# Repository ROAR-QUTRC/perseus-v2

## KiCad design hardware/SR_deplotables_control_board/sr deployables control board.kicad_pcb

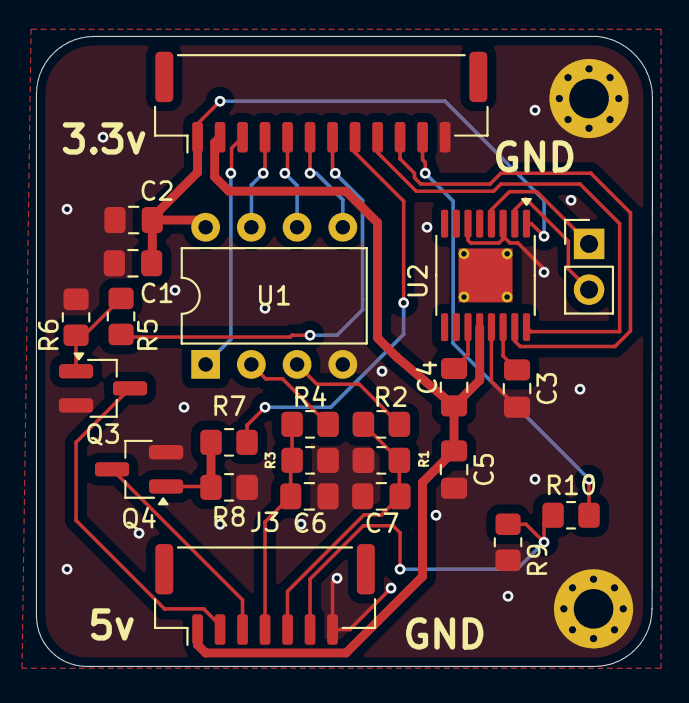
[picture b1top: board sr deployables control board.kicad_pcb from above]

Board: 2 copper layers, 34.2 x 35.0 mm, 26 parts (0 on the bottom side), 25 nets.

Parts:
C1: 100nF; C_0805_2012Metric_Pad1.18x1.45mm_HandSolder
C2, C6, C7: 10nF; C_0805_2012Metric_Pad1.18x1.45mm_HandSolder
C3: 2.2uF 6.3v; C_0805_2012Metric_Pad1.18x1.45mm_HandSolder
C4: 0.01uF, 16v ceramic X7R; C_0805_2012Metric_Pad1.18x1.45mm_HandSolder
C5: 10uF; C_0805_2012Metric_Pad1.18x1.45mm_HandSolder
H1: M1; MountingHole_2.2mm_M2_Pad_Via
H2: M2; MountingHole_2.2mm_M2_Pad_Via
J1: Conn_01x12_Pin; JST_GH_BM12B-GHS-TBT_1x12-1MP_P1.25mm_Vertical
J2: Conn_01x02_Pin; PinHeader_1x02_P2.54mm_Vertical
J3: Conn_01x07_Pin; JST_GH_BM07B-GHS-TBT_1x07-1MP_P1.25mm_Vertical
Q3, Q4: 2N7002; SOT-23_Handsoldering
R1, R3, R6, R8, R9: 10k; R_0805_2012Metric_Pad1.20x1.40mm_HandSolder
R2, R4, R10: 20k; R_0805_2012Metric_Pad1.20x1.40mm_HandSolder
R5, R7: 100; R_0805_2012Metric_Pad1.20x1.40mm_HandSolder
U1: MCP3002; DIP-8_W7.62mm
U2: DRV8833PW; TSSOP-16-1EP_4.4x5mm_P0.65mm_EP3x3mm_ThermalVias

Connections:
+3.3V: C1.1, C2.1, J1.1, U1.8 (VDD/VREF), U2.1 (~SLEEP)
AIN1: J1.9, U2.16 (AIN1)
AIN2: J1.10, U2.15 (AIN2)
CH0: C6.1, J3.4, R3.1, R4.1
CH1: C7.2, J3.5, R1.2, R2.1
CLK: J1.4, U1.7 (CLK)
CS: J1.3, U1.1 (~CS/SHDN)
DRAIN1: J3.2, Q3.3 (D)
DRAIN2: J3.3, Q4.3 (D)
GATE1: J1.7, R5.1
GATE2: J1.8, R7.1
GND: C1.2, C2.2, C3.2, C5.2, C6.2, C7.1, H1.1, H2.1, J1.12, J3.7, Q3.2 (S), Q4.2 (S), R1.1, R3.2, R6.1, R8.1, R9.2, U1.4 (VSS), U2.3 (AISEN), U2.6 (BISEN), U2.13 (GND)
MISO: J1.5, U1.6 (DOUT)
MOSI: J1.6, U1.5 (DIN)
unnamed: J2.1, U2.4 (AOUT2)
unnamed: J2.2, U2.2 (AOUT1)
unnamed: J3.6, R9.1, R10.1
unnamed: Q3.1 (G), R5.2, R6.2
unnamed: Q4.1 (G), R7.2, R8.2
unnamed: R4.2, U1.2 (CH0)
unnamed: R2.2, U1.3 (CH1)
unnamed: C4.2, U2.11 (VCP)
unnamed: C3.1, U2.14 (VINT)
SWITCH: J1.11, R10.2
VM: C4.1, C5.1, J1.2, J3.1, U2.12 (VM)

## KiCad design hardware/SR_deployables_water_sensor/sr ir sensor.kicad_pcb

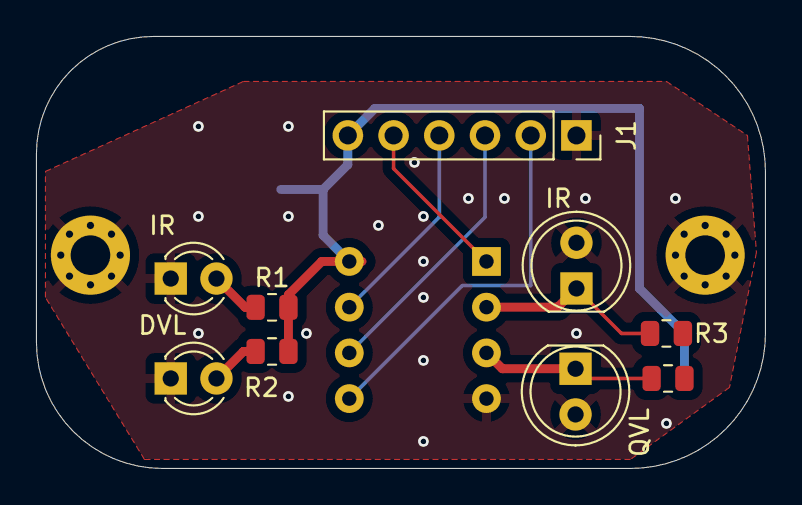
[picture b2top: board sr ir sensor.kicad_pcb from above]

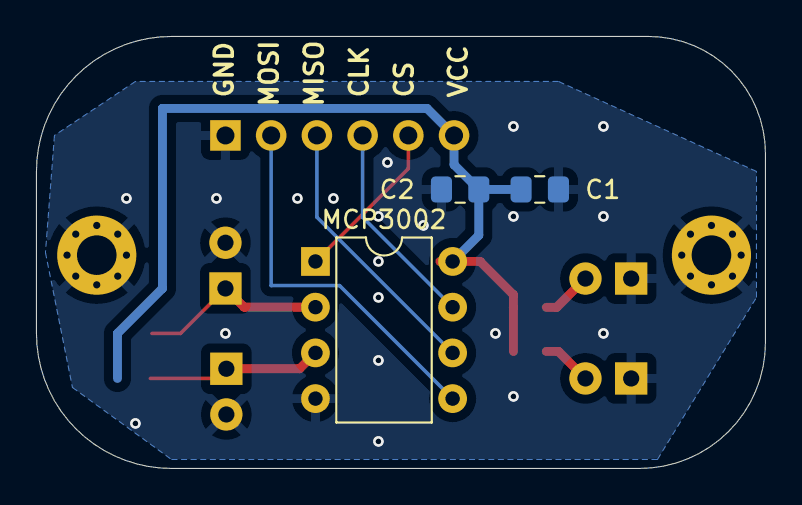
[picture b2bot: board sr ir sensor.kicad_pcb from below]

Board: 2 copper layers, 40.5 x 24.0 mm, 14 parts (3 on the bottom side), 10 nets.

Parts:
C1: 100nF; C_0805_2012Metric_Pad1.18x1.45mm_HandSolder
C2: 10nF; C_0805_2012Metric_Pad1.18x1.45mm_HandSolder
DVL: LED; LED_D3.0mm_Clear
H1: M1; MountingHole_2.2mm_M2_Pad_Via
H2: M2; MountingHole_2.2mm_M2_Pad_Via
IR: BPW40; LED_D5.0mm_Clear
IR#2: LED; LED_D3.0mm_Clear
J1: Pin_Connector; PinSocket_1x06_P2.54mm_Vertical
MCP3002: MCP3002; DIP-8_W7.62mm
QVL: BPW40; LED_D5.0mm_Clear
R1, R2, R3, R4: R; R_0805_2012Metric

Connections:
+3.3V: C1.1, C2.1, J1.6, MCP3002.8 (VDD/VREF), R1.2, R2.2, R3.2, R4.2
CH0: IR.1 (C), MCP3002.2 (CH0), R4.1
CH1: MCP3002.3 (CH1), QVL.1 (C), R3.1
CLK: J1.4, MCP3002.7 (CLK)
CS: J1.5, MCP3002.1 (~CS/SHDN)
GND: C1.2, C2.2, DVL.1 (K), H1.1, H2.1, IR.2 (E), IR#2.1 (K), J1.1, MCP3002.4 (VSS), QVL.2 (E)
MISO: J1.3, MCP3002.6 (DOUT)
MOSI: J1.2, MCP3002.5 (DIN)
unnamed: IR#2.2 (A), R1.1
unnamed: DVL.2 (A), R2.1

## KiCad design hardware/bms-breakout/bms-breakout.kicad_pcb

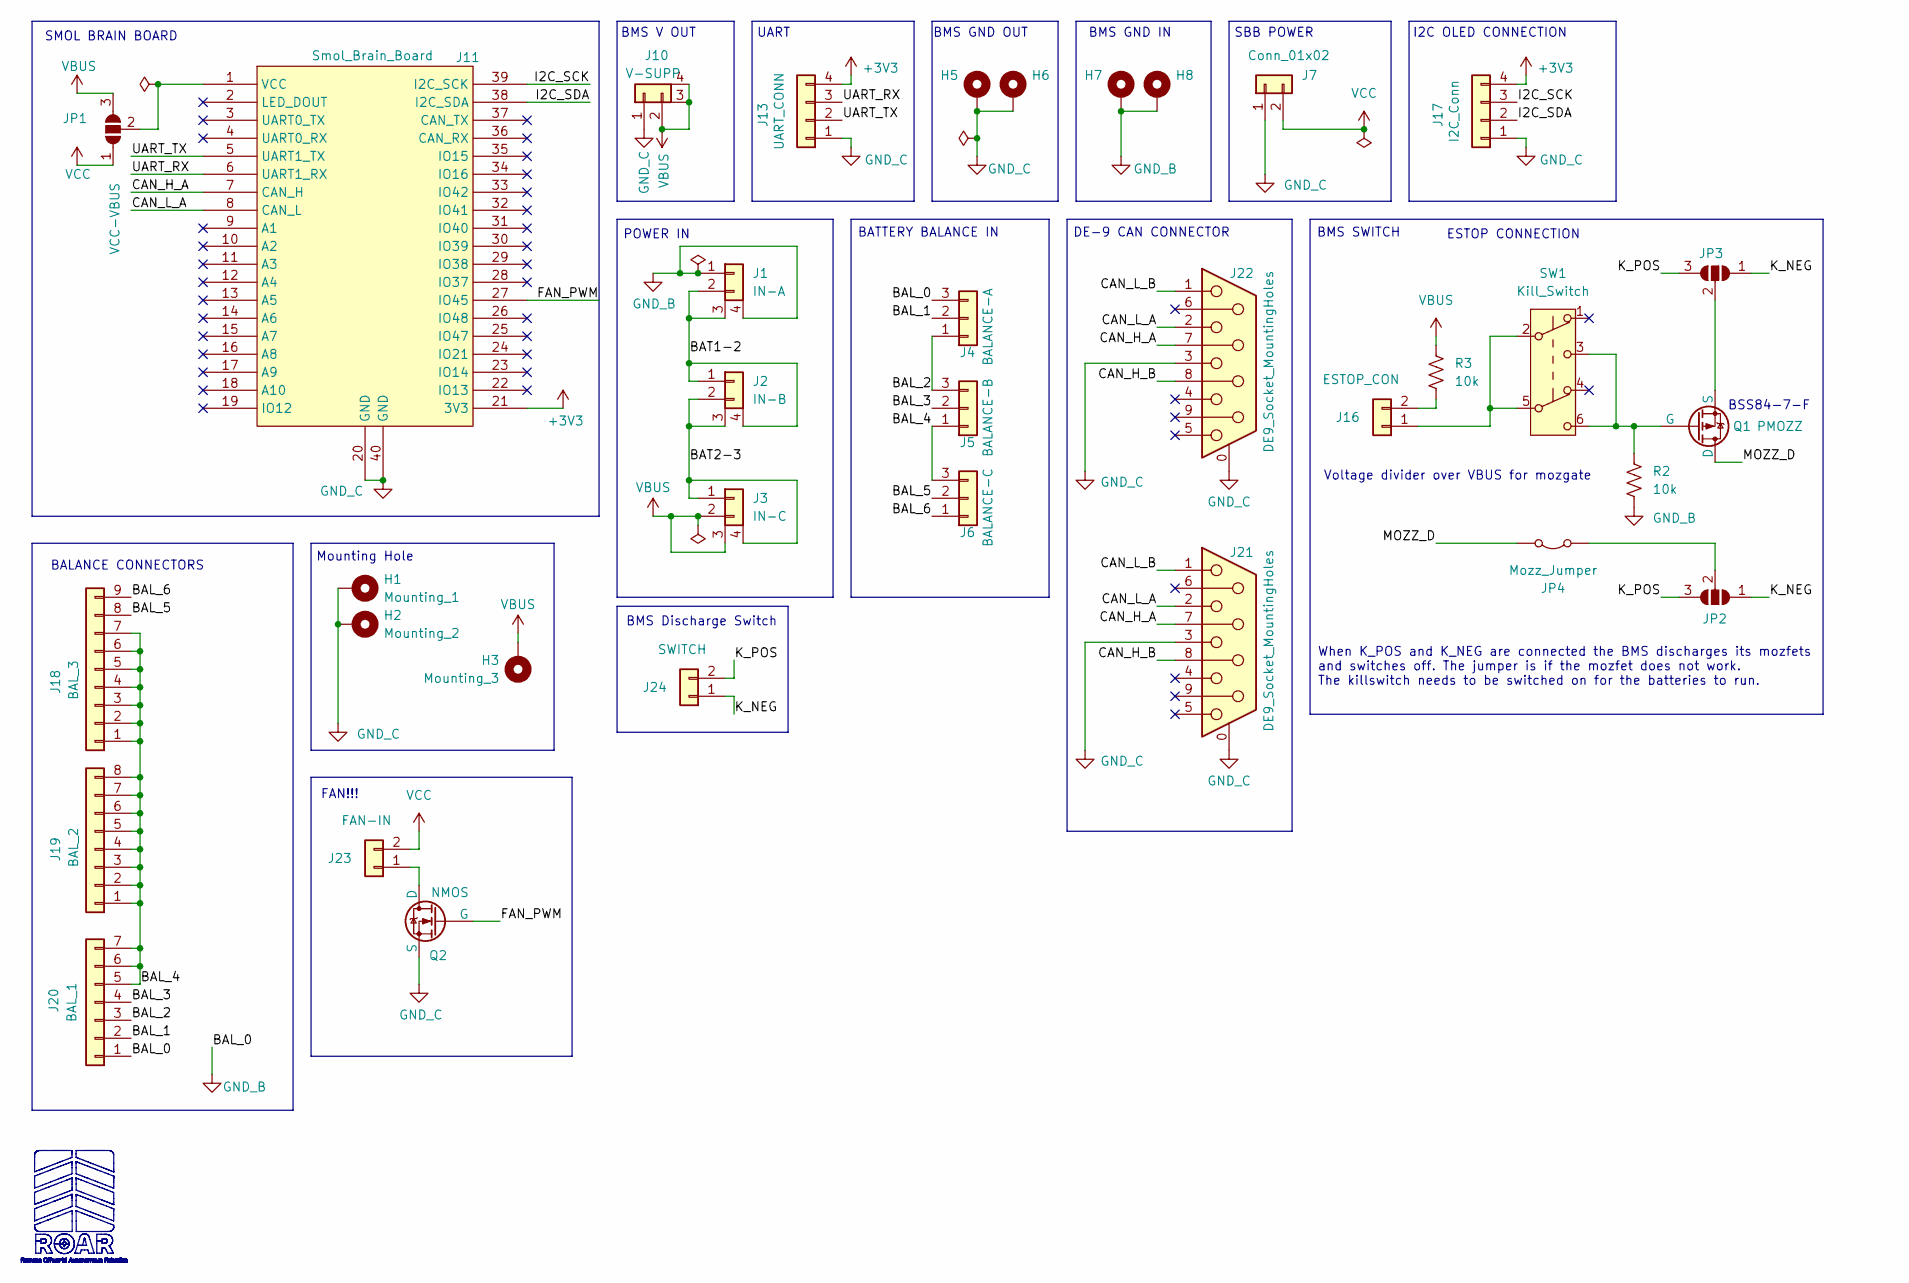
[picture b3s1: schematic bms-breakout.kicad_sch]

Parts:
H1: Mounting_1; MountingHole_3.2mm_M3_Pad_Via
H2: Mounting_2; MountingHole_3.2mm_M3_Pad_Via
H3: Mounting_3; MountingHole_3.2mm_M3_Pad_Via
H5, H6: BMS_OUT; MountingHole_3.5mm_Pad_Via
H7, H8: BMS_IN; MountingHole_3.5mm_Pad_Via
J1: IN-A; AMASS_XT90PW-M_1x02_P10.90mm_Horizontal
J2: IN-B; AMASS_XT90PW-M_1x02_P10.90mm_Horizontal
J3: IN-C; AMASS_XT90PW-M_1x02_P10.90mm_Horizontal
J4: BALANCE-A; JST_XH_S3B-XH-A-1_1x03_P2.50mm_Horizontal
J5: BALANCE-B; JST_XH_S3B-XH-A-1_1x03_P2.50mm_Horizontal
J6: BALANCE-C; JST_XH_S3B-XH-A-1_1x03_P2.50mm_Horizontal
J7: Conn_01x02; AMASS_XT30PW-M_1x02_P2.50mm_Horizontal
J10: V-SUPP; AMASS_XT90PW-M_1x02_P10.90mm_Horizontal
J11: Smol_Brain_Board
J13: UART_CONN; JST_XH_S4B-XH-A_1x04_P2.50mm_Horizontal
J16: ESTOP_CON; JST_XH_B2B-XH-A_1x02_P2.50mm_Vertical
J17: I2C_Conn; JST_XH_S4B-XH-A_1x04_P2.50mm_Horizontal
J18: BAL_3; JST_XH_S9B-XH-A_1x09_P2.50mm_Horizontal
J19: BAL_2; JST_XH_S8B-XH-A_1x08_P2.50mm_Horizontal
J20: BAL_1; JST_XH_S7B-XH-A_1x07_P2.50mm_Horizontal
J21, J22: DE9_Socket_MountingHoles; DSUB-9_Socket_Horizontal_P2.77x2.84mm_EdgePinOffset4.94mm_H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
J23: FAN-IN; JST_XH_B2B-XH-A_1x02_P2.50mm_Vertical
J24: SWITCH; JST_XH_B2B-XH-A_1x02_P2.50mm_Vertical
JP1: VCC-VBUS; SolderJumper-3_P1.3mm_Open_RoundedPad1.0x1.5mm
JP2: Drain_Side; SolderJumper-3_P1.3mm_Open_RoundedPad1.0x1.5mm
JP3: Source_Side; SolderJumper-3_P1.3mm_Open_RoundedPad1.0x1.5mm
JP4: Mozz_Jumper; SolderJumper-2_P1.3mm_Bridged_RoundedPad1.0x1.5mm
Q1: PMOZZ; SOT-23-3
Q2: NMOS; SOT-23-3
R2, R3: 10k; R_0805_2012Metric_Pad1.20x1.40mm_HandSolder
SW1: Kill_Switch; SW_Tactile_Straight_KSA0Axx1LFTR

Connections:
+3V3: J11.21 (3V3), J13.4, J17.4
/BAL_1: J4.2, J20.2
/BAL_2: J4.1, J5.3, J20.3
/BAL_3: J5.2, J20.4
/BAL_4: J5.1, J6.3, J18.1, J18.2, J18.3, J18.4, J18.5, J18.6, J18.7, J19.1, J19.2, J19.3, J19.4, J19.5, J19.6, J19.7, J19.8, J20.5, J20.6, J20.7
/BAL_5: J6.2, J18.8
/BAL_6: J6.1, J18.9
/BAT1-2: J1.2, J1.3 (M1), J2.1, J2.4 (M1)
/BAT2-3: J2.2, J2.3 (M1), J3.1, J3.4 (M1)
/CAN_H_A: J11.7 (CAN_H), J21.7, J22.7
/CAN_H_B: J21.8, J22.8
/CAN_L_A: J11.8 (CAN_L), J21.2, J22.2
/CAN_L_B: J21.1, J22.1
/FAN_PWM: J11.27 (IO45), Q2.2 (G)
/I2C_SCK: J11.39 (I2C_SCK), J17.3
/I2C_SDA: J11.38 (I2C_SDA), J17.2
/K_NEG: J24.1, JP2.1 (A), JP3.1 (A)
/K_POS: J24.2, JP2.3 (B), JP3.3 (B)
/MOZZ_D: JP4.1 (A), Q1.1 (D)
/UART_RX: J11.6 (UART1_RX), J13.3
/UART_TX: J11.5 (UART1_TX), J13.2
GND_B: H7.1, H8.1, J1.1, J1.4 (M1), J4.3, J20.1, R2.2
GND_C: H1.1, H2.1, H5.1, H6.1, J7.1, J10.1, J11.20 (GND), J11.40 (GND), J13.1, J17.1, J21.0 (PAD), J21.3, J22.0 (PAD), J22.3, Q2.3 (S)
unnamed: J11.1 (VCC), JP1.2 (C)
unnamed: J16.1, SW1.2 (B), SW1.5 (B)
unnamed: J16.2, R3.2
unnamed: J23.1, Q2.1 (D)
unnamed: JP2.2 (C), JP4.2 (B)
unnamed: JP3.2 (C), Q1.3 (S)
unnamed: Q1.2 (G), R2.1, SW1.3 (C), SW1.6 (C)
VBUS: H3.1, J3.2, J3.3 (M1), J10.2, J10.3 (M1), J10.4 (M1), JP1.3 (B), R3.1
VCC: J7.2, J23.2, JP1.1 (A)

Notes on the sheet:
Mounting Hole
I2C OLED CONNECTION
BMS SWITCH
BALANCE CONNECTORS
BSS84-7-F
BMS Discharge Switch
BMS GND OUT
UART
BATTERY BALANCE IN
ESTOP CONNECTION
SBB POWER
When K_POS and K_NEG are connected the BMS discharges its mozfets and switches off. The jumper is if the mozfet does not work. The killswitch needs to be switched on for the batteries to run.
DE-9 CAN CONNECTOR
Voltage divider over VBUS for mozgate
BMS V OUT
BMS GND IN
FAN!!!
POWER IN
SMOL BRAIN BOARD

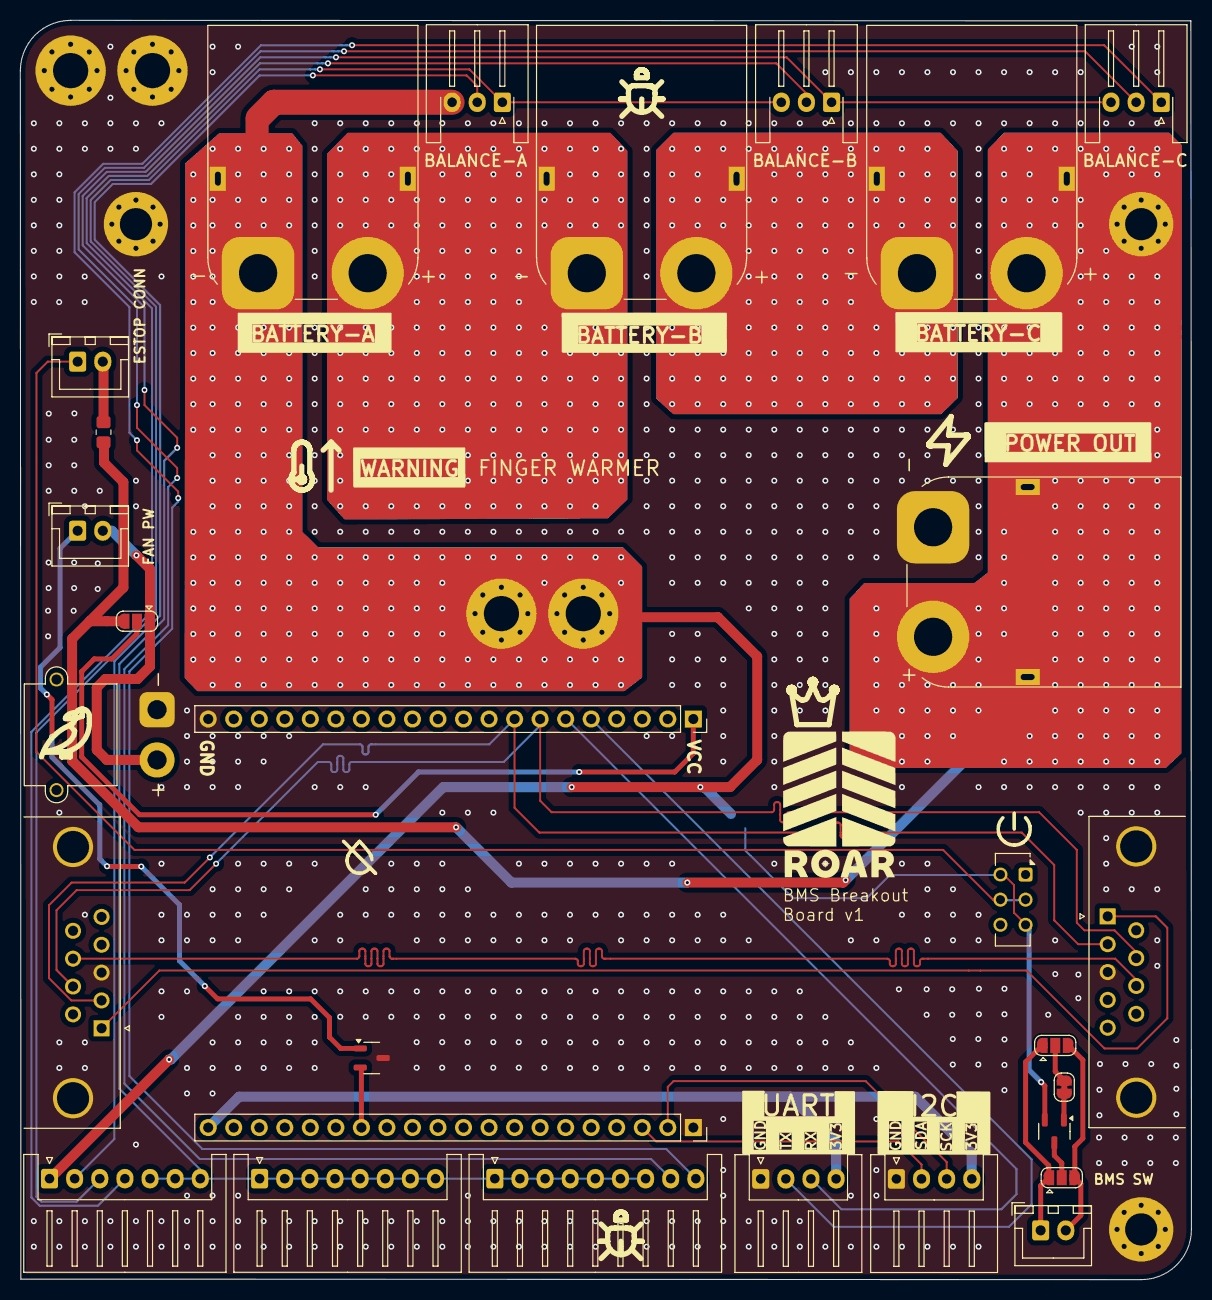
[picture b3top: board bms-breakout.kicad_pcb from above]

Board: 2 copper layers, 116.5 x 125.3 mm, 35 parts (1 on the bottom side), 32 nets.

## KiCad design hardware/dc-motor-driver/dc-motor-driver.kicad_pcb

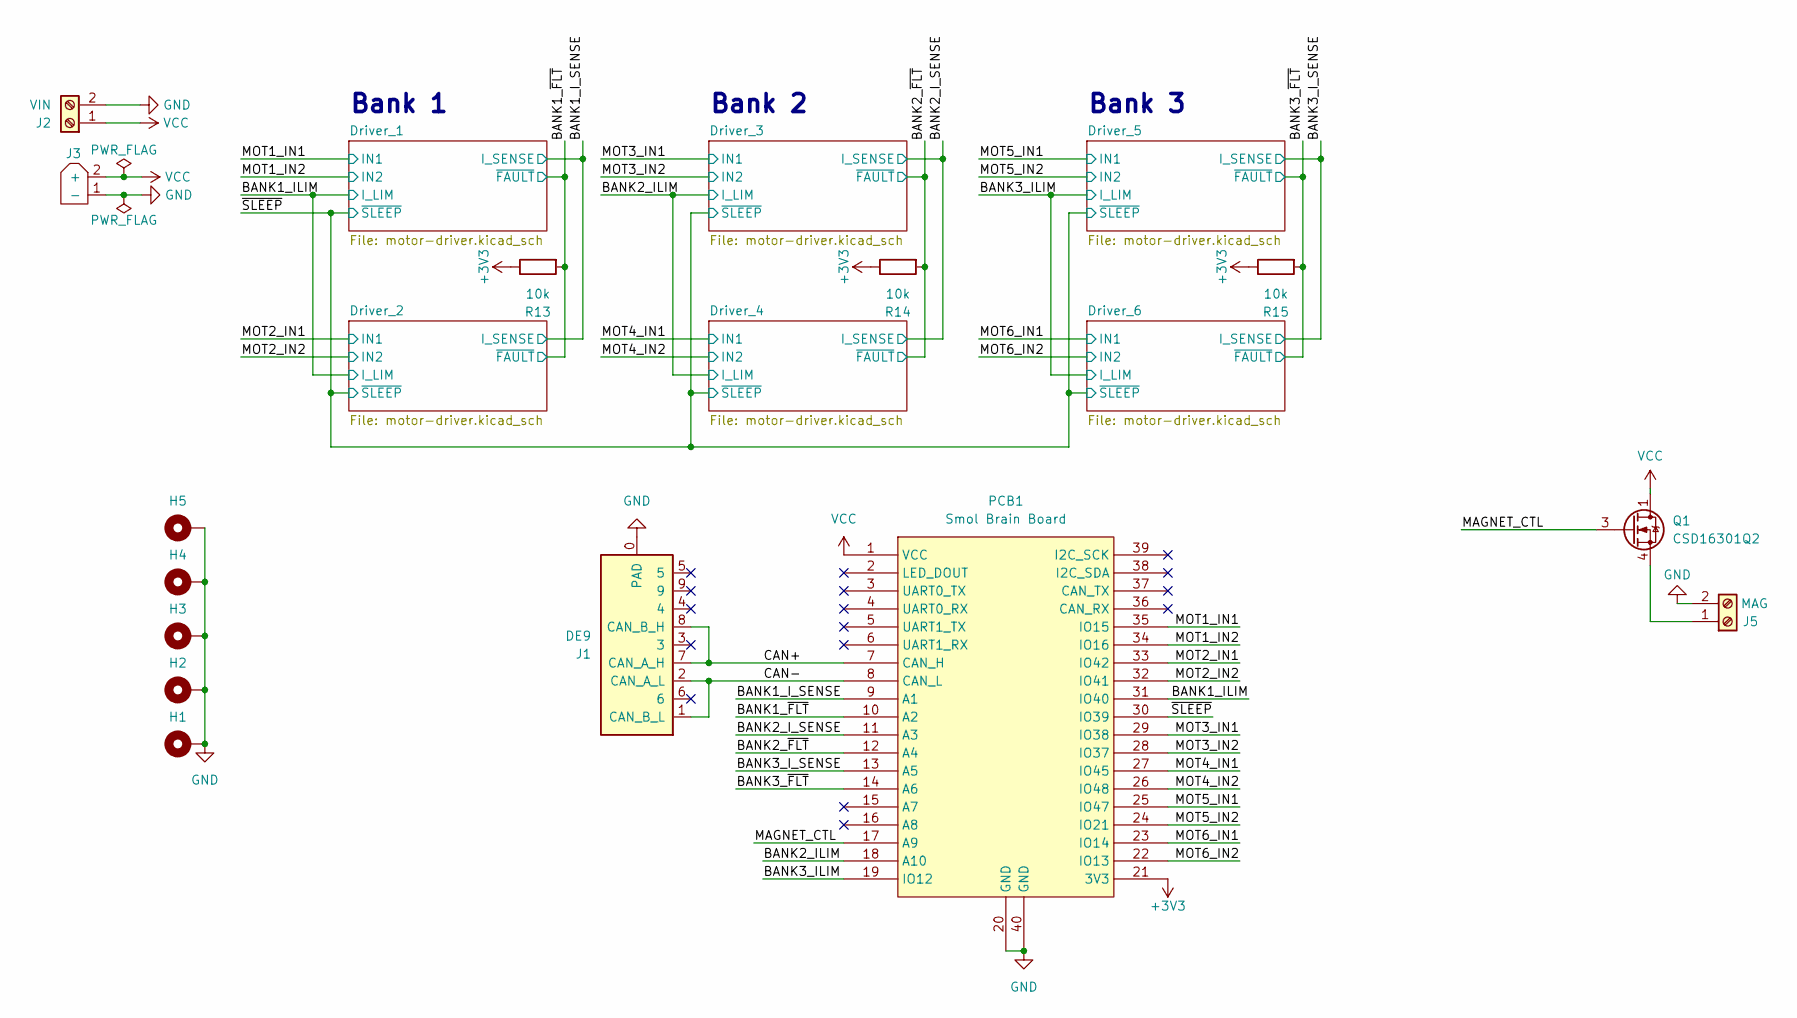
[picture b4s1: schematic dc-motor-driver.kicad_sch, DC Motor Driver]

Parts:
H1, H2, H3, H4, H5: MountingHole_Pad; MountingHole_3mm_Pad
J1: DE9; A-DF_09_A_KG-T2S
J2: VIN; TerminalBlock_4Ucon_1x02_P3.50mm_Horizontal
J3: AMASS_XT60PW-M_1x02_P7.20mm_Horizontal
J5: MAG; TerminalBlock_4Ucon_1x02_P3.50mm_Horizontal
PCB1: Smol Brain Board; Smol_Brain_Board
Q1: CSD16301Q2; Texas_DQK
R13, R14, R15: 10k; R_0603_1608Metric

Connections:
+3V3: PCB1.21 (3V3), R13.2, R14.2, R15.2; also elsewhere on the board
/BANK1_ILIM: PCB1.31 (IO40); also elsewhere on the board
/BANK1_I_SENSE: PCB1.9 (A1); also elsewhere on the board
/BANK1_~FLT: PCB1.10 (A2), R13.1; also elsewhere on the board
/BANK2_ILIM: PCB1.18 (A10); also elsewhere on the board
/BANK2_I_SENSE: PCB1.11 (A3); also elsewhere on the board
/BANK2_~FLT: PCB1.12 (A4), R14.1; also elsewhere on the board
/BANK3_ILIM: PCB1.19 (IO12); also elsewhere on the board
/BANK3_I_SENSE: PCB1.13 (A5); also elsewhere on the board
/BANK3_~FLT: PCB1.14 (A6), R15.1; also elsewhere on the board
/CAN+: J1.7 (CAN_A_H), J1.8 (CAN_B_H), PCB1.7 (CAN_H)
/CAN-: J1.1 (CAN_B_L), J1.2 (CAN_A_L), PCB1.8 (CAN_L)
/MAGNET_CTL: PCB1.17 (A9), Q1.3 (G)
/MOT1_IN1: PCB1.35 (IO15); also elsewhere on the board
/MOT1_IN2: PCB1.34 (IO16); also elsewhere on the board
/MOT2_IN1: PCB1.33 (IO42); also elsewhere on the board
/MOT2_IN2: PCB1.32 (IO41); also elsewhere on the board
/MOT3_IN1: PCB1.29 (IO38); also elsewhere on the board
/MOT3_IN2: PCB1.28 (IO37); also elsewhere on the board
/MOT4_IN1: PCB1.27 (IO45); also elsewhere on the board
/MOT4_IN2: PCB1.26 (IO48); also elsewhere on the board
/MOT5_IN1: PCB1.25 (IO47); also elsewhere on the board
/MOT5_IN2: PCB1.24 (IO21); also elsewhere on the board
/MOT6_IN1: PCB1.23 (IO14); also elsewhere on the board
/MOT6_IN2: PCB1.22 (IO13); also elsewhere on the board
/~SLEEP: PCB1.30 (IO39); also elsewhere on the board
GND: H1.1, H2.1, H3.1, H4.1, H5.1, J1.0 (PAD), J2.2, J3.1 (-), J5.2, PCB1.20 (GND), PCB1.40 (GND); also elsewhere on the board
unnamed: J5.1, Q1.4 (S), Q1.7 (S)
VCC: J2.1, J3.2 (+), PCB1.1 (VCC), Q1.1 (D), Q1.2 (D), Q1.5 (D), Q1.6 (D), Q1.8 (D); also elsewhere on the board

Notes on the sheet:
Bank 2
Bank 3
Bank 1

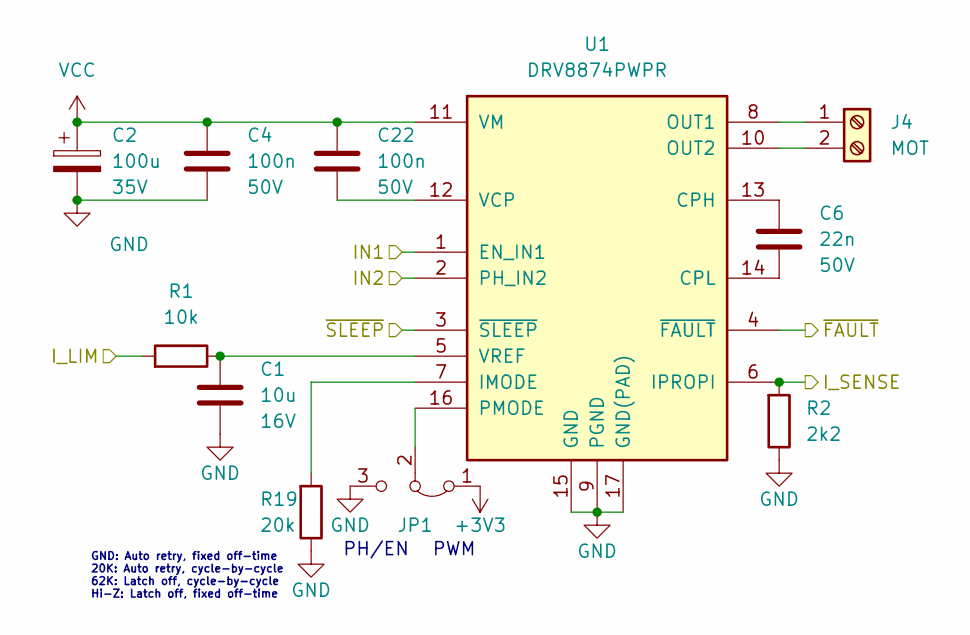
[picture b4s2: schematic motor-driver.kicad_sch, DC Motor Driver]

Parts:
C1: 10u; C_0805_2012Metric
C2: 100u; CP_Elec_6.3x7.7
C4, C22: 100n; C_0603_1608Metric
C6: 22n; C_0603_1608Metric
J4: MOT; TerminalBlock_4Ucon_1x02_P3.50mm_Horizontal
JP1: Jumper_3_Bridged12; SolderJumper-3_P1.3mm_Bridged12_RoundedPad1.0x1.5mm
R1: 10k; R_0603_1608Metric
R2: 2k2; R_0603_1608Metric
R19: 20k; R_0603_1608Metric
U1: DRV8874PWPR; HTSSOP-16-1EP_4.4x5mm_P0.65mm_EP3.4x5mm_Mask2.66x2.46mm_The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

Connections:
+3V3: JP1.1 (A); also elsewhere on the board
/BANK1_ILIM: R1.1; also elsewhere on the board
/BANK1_I_SENSE: R2.1, U1.6 (IPROPI); also elsewhere on the board
/BANK1_~FLT: U1.4 (~FAULT); also elsewhere on the board
/MOT1_IN1: U1.1 (EN_IN1); also elsewhere on the board
/MOT1_IN2: U1.2 (PH_IN2); also elsewhere on the board
/~SLEEP: U1.3 (~SLEEP); also elsewhere on the board
GND: C1.2, C2.2, C4.2, JP1.3 (B), R2.2, R19.2, U1.9 (PGND), U1.15 (GND), U1.17 (GND(PAD)); also elsewhere on the board
unnamed: J4.1, U1.8 (OUT1)
unnamed: J4.2, U1.10 (OUT2)
unnamed: JP1.2 (C), U1.16 (PMODE)
unnamed: C6.1, U1.13 (CPH)
unnamed: C6.2, U1.14 (CPL)
unnamed: R19.1, U1.7 (IMODE)
unnamed: C22.2, U1.12 (VCP)
unnamed: C1.1, R1.2, U1.5 (VREF)
VCC: C2.1, C4.1, C22.1, U1.11 (VM); also elsewhere on the board

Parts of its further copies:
C3, C7, C9, C13, C15: 10u; C_0805_2012Metric
C5, C10, C11, C16, C17, C23, C28, C29, C34, C35: 100n; C_0603_1608Metric
C8, C14, C20, C26, C32: 100u; CP_Elec_6.3x7.7
C12, C18, C24, C30, C36: 22n; C_0603_1608Metric
J6, J8, J10, J12, J14: MOT; TerminalBlock_4Ucon_1x02_P3.50mm_Horizontal
JP2, JP3, JP4, JP5, JP6: Jumper_3_Bridged12; SolderJumper-3_P1.3mm_Bridged12_RoundedPad1.0x1.5mm
R3, R5, R6, R8, R9: 2k2; R_0603_1608Metric
R4, R7, R10, R11, R12: 10k; R_0603_1608Metric
R20, R21, R22, R23, R24: 20k; R_0603_1608Metric
U2, U3, U4, U5, U6: DRV8874PWPR; HTSSOP-16-1EP_4.4x5mm_P0.65mm_EP3.4x5mm_Mask2.66x2.46mm_The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

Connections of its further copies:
+3V3: JP2.1 (A), JP3.1 (A), JP4.1 (A), JP5.1 (A), JP6.1 (A); also elsewhere on the board
/BANK1_ILIM: R4.1; also elsewhere on the board
/BANK1_I_SENSE: R3.1, U2.6 (IPROPI); also elsewhere on the board
/BANK1_~FLT: U2.4 (~FAULT); also elsewhere on the board
/BANK2_ILIM: R7.1, R10.1; also elsewhere on the board
/BANK2_I_SENSE: R5.1, R6.1, U3.6 (IPROPI), U4.6 (IPROPI); also elsewhere on the board
/BANK2_~FLT: U3.4 (~FAULT), U4.4 (~FAULT); also elsewhere on the board
/BANK3_ILIM: R11.1, R12.1; also elsewhere on the board
/BANK3_I_SENSE: R8.1, R9.1, U5.6 (IPROPI), U6.6 (IPROPI); also elsewhere on the board
/BANK3_~FLT: U5.4 (~FAULT), U6.4 (~FAULT); also elsewhere on the board
/MOT2_IN1: U2.1 (EN_IN1); also elsewhere on the board
/MOT2_IN2: U2.2 (PH_IN2); also elsewhere on the board
/MOT3_IN1: U3.1 (EN_IN1); also elsewhere on the board
/MOT3_IN2: U3.2 (PH_IN2); also elsewhere on the board
/MOT4_IN1: U4.1 (EN_IN1); also elsewhere on the board
/MOT4_IN2: U4.2 (PH_IN2); also elsewhere on the board
/MOT5_IN1: U5.1 (EN_IN1); also elsewhere on the board
/MOT5_IN2: U5.2 (PH_IN2); also elsewhere on the board
/MOT6_IN1: U6.1 (EN_IN1); also elsewhere on the board
/MOT6_IN2: U6.2 (PH_IN2); also elsewhere on the board
/~SLEEP: U2.3 (~SLEEP), U3.3 (~SLEEP), U4.3 (~SLEEP), U5.3 (~SLEEP), U6.3 (~SLEEP); also elsewhere on the board
GND: C3.2, C5.2, C7.2, C8.2, C9.2, C10.2, C11.2, C13.2, C14.2, C15.2, C16.2, C17.2, C20.2, C26.2, C32.2, JP2.3 (B), JP3.3 (B), JP4.3 (B), JP5.3 (B), JP6.3 (B), R3.2, R5.2, R6.2, R8.2, R9.2, R20.2, R21.2, R22.2, R23.2, R24.2, U2.9 (PGND), U2.15 (GND), U2.17 (GND(PAD)), U3.9 (PGND), U3.15 (GND), U3.17 (GND(PAD)), U4.9 (PGND), U4.15 (GND), U4.17 (GND(PAD)), U5.9 (PGND), U5.15 (GND), U5.17 (GND(PAD)), U6.9 (PGND), U6.15 (GND), U6.17 (GND(PAD)); also elsewhere on the board
unnamed: J6.1, U2.8 (OUT1)
unnamed: J6.2, U2.10 (OUT2)
unnamed: J8.1, U3.8 (OUT1)
unnamed: J8.2, U3.10 (OUT2)
unnamed: J10.1, U4.8 (OUT1)
unnamed: J10.2, U4.10 (OUT2)
unnamed: J12.1, U5.8 (OUT1)
unnamed: J12.2, U5.10 (OUT2)
unnamed: J14.1, U6.8 (OUT1)
unnamed: J14.2, U6.10 (OUT2)
unnamed: JP2.2 (C), U2.16 (PMODE)
unnamed: JP3.2 (C), U3.16 (PMODE)
unnamed: JP4.2 (C), U4.16 (PMODE)
unnamed: JP5.2 (C), U5.16 (PMODE)
unnamed: JP6.2 (C), U6.16 (PMODE)
unnamed: C12.1, U2.13 (CPH)
unnamed: C12.2, U2.14 (CPL)
unnamed: R20.1, U2.7 (IMODE)
unnamed: C23.2, U2.12 (VCP)
unnamed: C3.1, R4.2, U2.5 (VREF)
unnamed: C18.1, U3.13 (CPH)
unnamed: C18.2, U3.14 (CPL)
unnamed: R21.1, U3.7 (IMODE)
unnamed: C28.2, U3.12 (VCP)
unnamed: C7.1, R7.2, U3.5 (VREF)
unnamed: C24.1, U4.13 (CPH)
unnamed: C24.2, U4.14 (CPL)
unnamed: R22.1, U4.7 (IMODE)
unnamed: C29.2, U4.12 (VCP)
unnamed: C9.1, R10.2, U4.5 (VREF)
unnamed: C30.1, U5.13 (CPH)
unnamed: C30.2, U5.14 (CPL)
unnamed: R23.1, U5.7 (IMODE)
unnamed: C34.2, U5.12 (VCP)
unnamed: C13.1, R11.2, U5.5 (VREF)
unnamed: C36.1, U6.13 (CPH)
unnamed: C36.2, U6.14 (CPL)
unnamed: R24.1, U6.7 (IMODE)
unnamed: C35.2, U6.12 (VCP)
unnamed: C15.1, R12.2, U6.5 (VREF)
VCC: C5.1, C8.1, C10.1, C11.1, C14.1, C16.1, C17.1, C20.1, C23.1, C26.1, C28.1, C29.1, C32.1, C34.1, C35.1, U2.11 (VM), U3.11 (VM), U4.11 (VM), U5.11 (VM), U6.11 (VM); also elsewhere on the board

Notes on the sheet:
PWM
GND: Auto retry, fixed off-time 20K: Auto retry, cycle-by-cycle 62K: Latch off, cycle-by-cycle Hi-Z: Latch off, fixed off-time
PH/EN

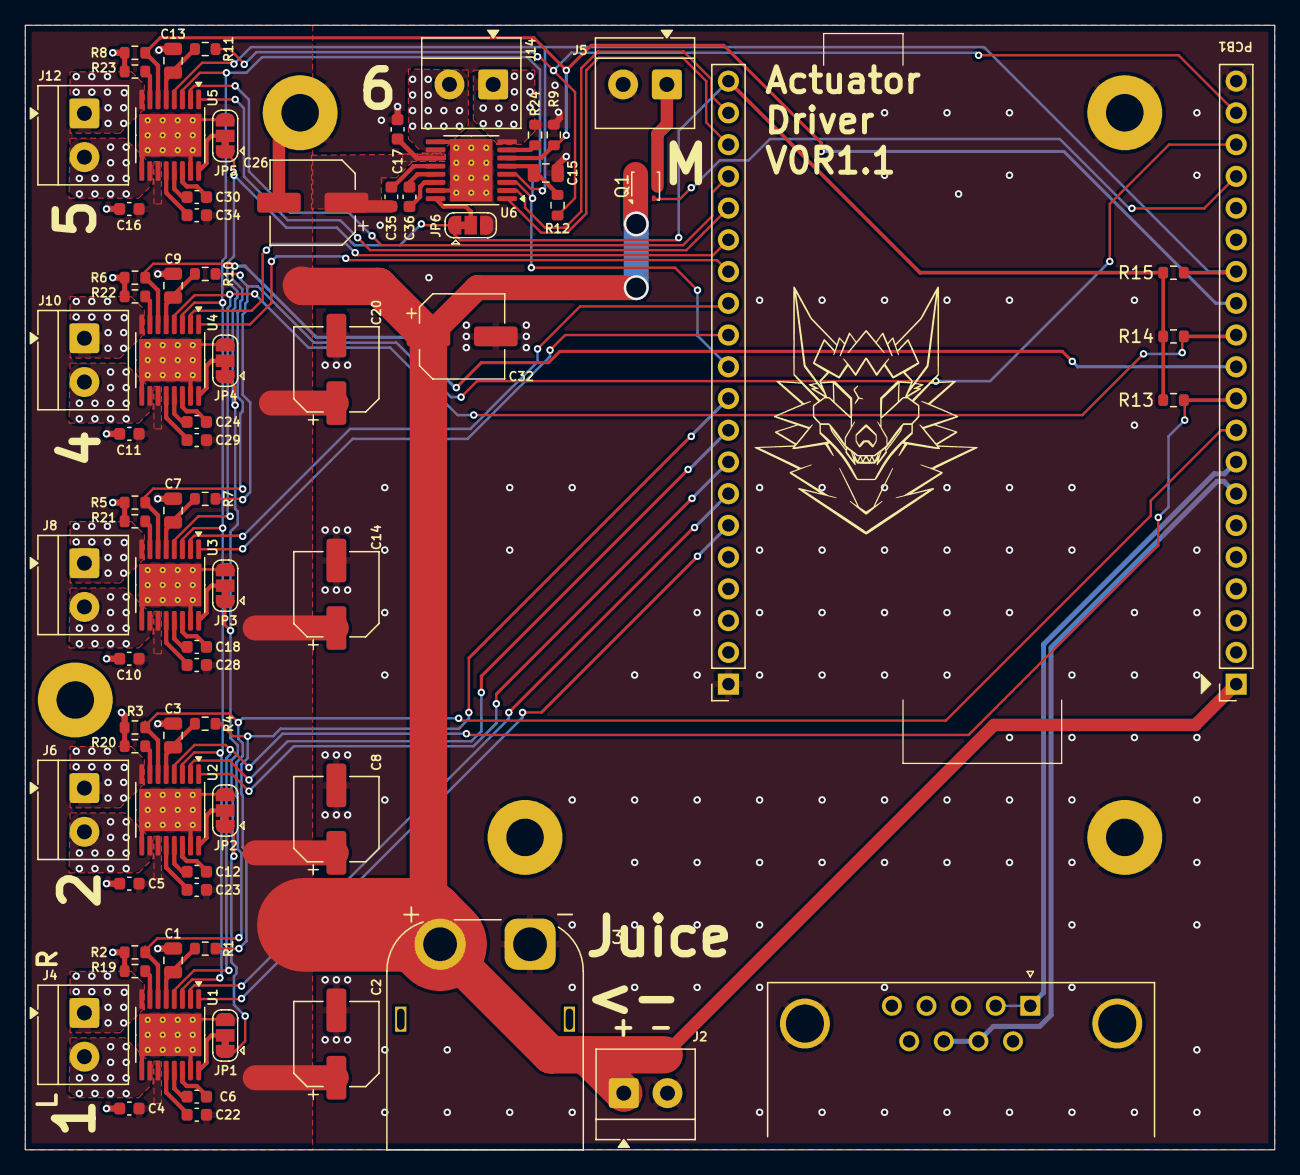
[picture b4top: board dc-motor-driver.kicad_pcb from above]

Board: 2 copper layers, 100.0 x 90.0 mm, 80 parts (0 on the bottom side), 77 nets.
